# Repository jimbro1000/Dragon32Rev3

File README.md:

# DRAGON 32 RECREATION Rev 3 #

This project started as a recreation of the SA2120 CPU Mainboard
for the 1982 Dragon Data **Dragon 32**

Everything (excluding modifications) is taken from the SA2120
schematics. Where this version changes is that the options to
use banks of 16K DRAM is gone, you must use 64K DRAMs, with it
goes all the extra circuitry for configuring the memory for
different types of chip.

The ROM is now a single 27C256 eprom with an option to switch
between two images using JP6 or to allow the rom to be
automatically selected from the PIA.

A second ROM selection jumper is available at JP3 to be used
when a 27C512 is fitted. This swaps the value to A15 between
high and low. When a 27C256 is fitted this must be set low.

Hidden on the back of the board is a solder pad jumper (JP7) that
also needs setting to handle a 27C256 or 27C512. Bridging pad
1 sets pin 22 of the rom to ground, using pad 3 sets the
pin to use the ROM select signal shared with pin 20. When a
27C512 is fitted this must be set to pad 1.

The video circuits have been isolated from the rest of the
board to improve output quality.

A second (internal) cartridge port has been added, by way of
a 2x20 header, along with an additional +5V/Gnd pickup point
for further internal expansion.

An optional 256K banking solution is incorporated using the
design for Stewart Orchard's upgrade board and GAL design.
<https://gitlab.com/sorchard001/dragon-256k-banker-board>

## Progress ##

In the current state (3.3) most of the board is tested except
for the additional audio capabilities, SAMx8 compatibility and
the logic controlled switching of keyboard configuration.

## Modifications ##

### Joysticks ###

The two joystick ports provide a second fire button capability
wired to consecutive keyboard rows, as per the Tandy CoCo.
Unless a two button joystick is used this make no difference to
the operation of the computer. It also requires the use of 6-pin
DIN sockets, these are pin compatible with the 5-pin originals
so a regular single button joystick can still be used.

The two extra buttons can also be disabled by omitting L3 and L4.

### Parallel Port ###

A jumper (JP2) has been introduced to bypass the logic inverter
on the STROBE line. When bypassed the parallel port should
operate as a communication port for DRIVEWIRE.

### Memory Addressing ###

The board is configurable between 32k and 64k ram addressing
using jumper JP1. In most scenarios there is no reason to
disable the 64k option.

The upgrade to 256K needs the 4164s swapping for 41256s. The
pre-bridged jumper at JP5 needs cutting. The SAM also needs 
to be replaced with a 74LS785. The optional components can 
then be fitted and should work without further alteration.

The required JED file for the GAL22V10 that drives the memory
banking is in the CPLD folder of the project.

The 256K upgrade can be replaced with a SAMx8 upgrade board.
This replaces the SAM chip and the tristate buffer that sits
between the RAM and the CPU, and also allows connection to
the second data path that goes to the VDG. With this in place
the DRAM (either 4164 or 41256) is redundant, as is the GAL 
that provides the 256K banker capability.

### Video Port ###

The board includes a third connector for the video mezzanine
card. This exposes the video board to the CPU side of the
data bus along with control signals that would permit 
programming of the video for additional features. With a 
stock 6847 that might be to include a programmable character
"rom" but I'm also working on a synthetic FPGA based replacement
for the 6847 that will allow much bigger changes such as 
swappable/programmable colour palettes.

### Audio ###

The board provides a position to mount a custom implementation
of the AY sound generator. This provides three channels of 
synthesised sound without using the CPU intensive system that
the Dragon comes with by default. The capabilities are the same
as those of the Spectrum 128 models. You can even mix the old
and new methods of sound generation to create more noise!

Theoretically other sound generators could be used but the AY
option provides a cheap, capable mechanism that follows a 
standard familiar to users of other computers from the era.

### Keyboard ###

The board places a GAL chip between the input register of
PIA 1 and the keyboard connector. The GAL could be ommitted
and jumpers used to hardwire the connections to either
Dragon or CoCo compatibility.

With a GAL in place the wiring is controlled by a jumper.

## Substitutions ##

Many of the original components are simply unobtainable or
just very hard (and expensive) to locate. The transistors
will need modern substitutes as the BC141, BC212 and 2N2369
are all obsolete but thankfully these are fairly run-of-the-mill
transistors and shouldn't cause any particular issues.

The CPU and PIAs are all fairly easy to obtain online
and possibly even new (MC6821s are still made and there
are lots of compatible alternatives). A and B rated components
should all be usable but make sure the processor is an "09e".
The Hitachi HD6309 is usable but may cause crashes in some
software due to lazy coding.

Ciaran Anscomb's samX4 can be used to replace the SAM
chip and can be configured to operate as a 74LS783 or a
74LS785 to suit.

### The Future ###

As these parts become harder to find it is inevitable that
replacements and redesigns will be needed. After much hard
work by the Dragon and CoCo community the *only* IC on the
required, that is not still made or in plentiful supply is
the MC6847 VDG (the LM1889 on the PAL board is also in
limited supply but there are ways around the issue).

The Hitachi HD6309 has been in production until recently due
to military supply contracts making it easily accessible and
at reasonable cost. Ultimately this will diminish but with
supplies still high it seems likely to be available for a long
time yet.

The MC6821 is available new but at eye watering prices as
it is only made in small batches. The WD65C21 is a direct
swap and in much higher supply making it generally cheaper
than remaining original NOS parts.

The LS and CD discrete logic chips are all generally easy
to obtain and all have more modern equivalents that can be
swapped in.

Some searching may be needed for the cartridge port connector.
A direct replacement part is listed in the EDAC catalogue but
is only made to demand which requires an order of some 200
units. Lower quality but compatible parts can be found online.

Ultimately all of the parts will become hard to obtain but
for the foreseeable future the board should remain viable.

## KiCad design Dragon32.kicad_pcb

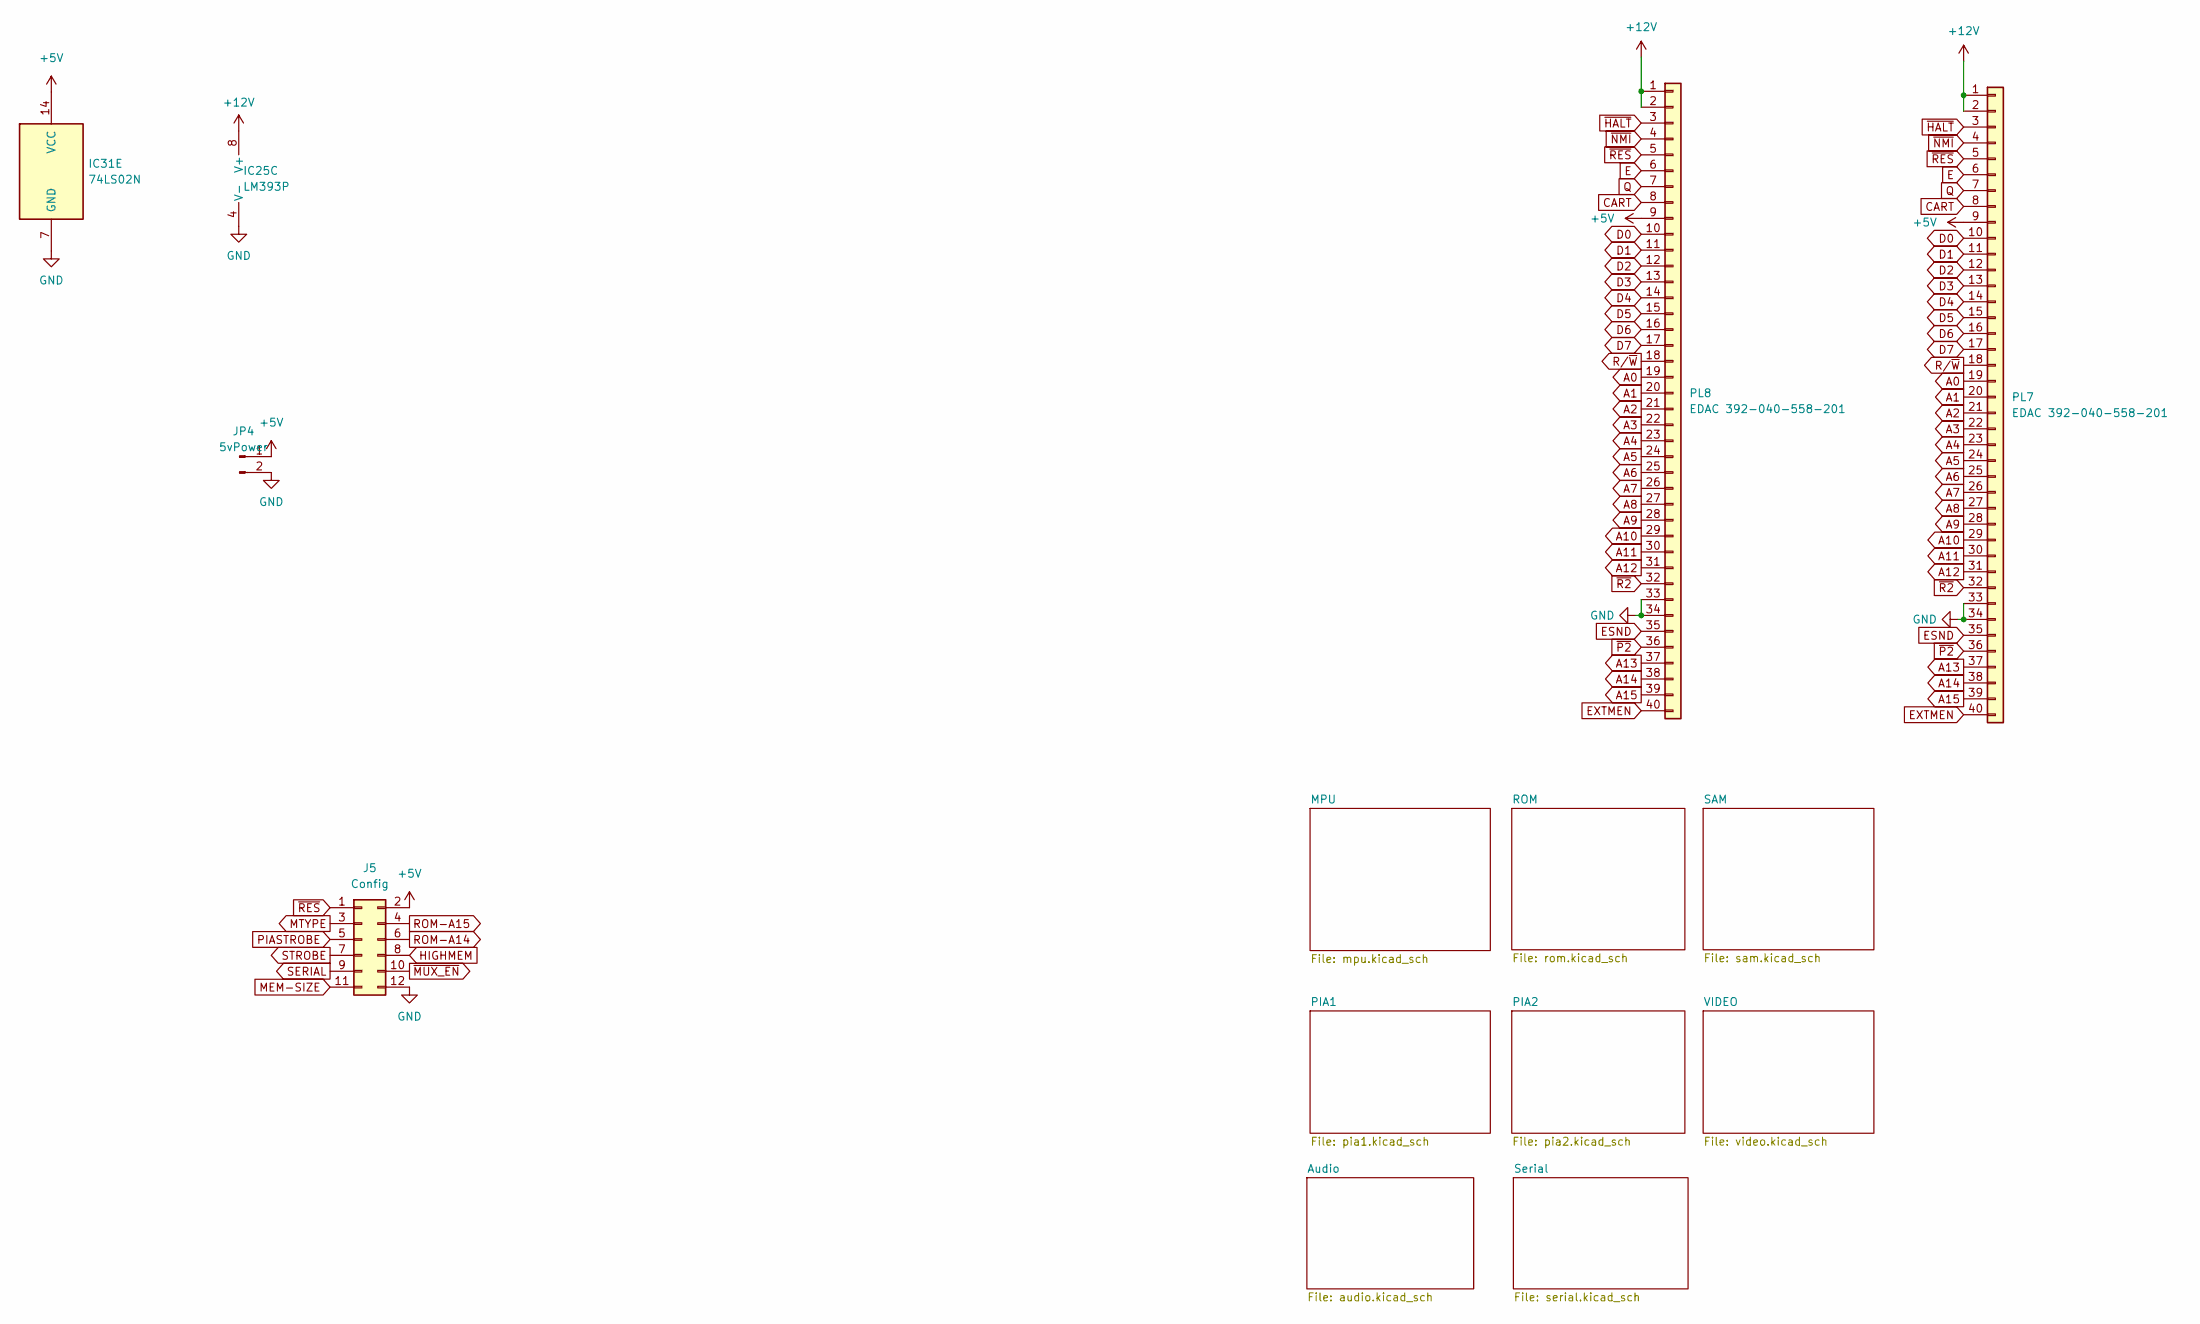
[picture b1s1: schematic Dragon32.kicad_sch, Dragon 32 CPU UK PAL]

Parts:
IC25: LM393P; DIP-8_W7.62mm; DigiKey 296-1398-5-ND
IC31: 74LS02N; DIP-14_W7.62mm; DigiKey 296-1627-5-ND
J5: Config; PinHeader_2x06_P2.54mm_Vertical
JP4: 5vPower; PinHeader_1x02_P2.54mm_Vertical
PL7: EDAC 392-040-558-201; Edge_2x20_P2.54mm_OvalMP; DigiKey 151-395-040-558-201-ND
PL8: EDAC 392-040-558-201; PinHeader_2x20_P2.54mm_Vertical; DigiKey 151-395-040-558-201-ND

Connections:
+5V: IC31.14 (VCC), J5.2, JP4.1, PL7.9, PL8.9; also elsewhere on the board
+12V: IC25.8 (V+), PL7.1, PL7.2, PL8.1, PL8.2; also elsewhere on the board
A0: PL7.19, PL8.19; also elsewhere on the board
A1: PL7.20, PL8.20; also elsewhere on the board
A2: PL7.21, PL8.21; also elsewhere on the board
A3: PL7.22, PL8.22; also elsewhere on the board
A4: PL7.23, PL8.23; also elsewhere on the board
A5: PL7.24, PL8.24; also elsewhere on the board
A6: PL7.25, PL8.25; also elsewhere on the board
A7: PL7.26, PL8.26; also elsewhere on the board
A8: PL7.27, PL8.27; also elsewhere on the board
A9: PL7.28, PL8.28; also elsewhere on the board
A10: PL7.29, PL8.29; also elsewhere on the board
A11: PL7.30, PL8.30; also elsewhere on the board
A12: PL7.31, PL8.31; also elsewhere on the board
A13: PL7.37, PL8.37; also elsewhere on the board
A14: PL7.38, PL8.38; also elsewhere on the board
A15: PL7.39, PL8.39; also elsewhere on the board
CART: PL7.8, PL8.8; also elsewhere on the board
D0: PL7.10, PL8.10; also elsewhere on the board
D1: PL7.11, PL8.11; also elsewhere on the board
D2: PL7.12, PL8.12; also elsewhere on the board
D3: PL7.13, PL8.13; also elsewhere on the board
D4: PL7.14, PL8.14; also elsewhere on the board
D5: PL7.15, PL8.15; also elsewhere on the board
D6: PL7.16, PL8.16; also elsewhere on the board
D7: PL7.17, PL8.17; also elsewhere on the board
E: PL7.6, PL8.6; also elsewhere on the board
ESND: PL7.35, PL8.35; also elsewhere on the board
EXTMEN: PL7.40, PL8.40; also elsewhere on the board
HIGHMEM: J5.8; also elsewhere on the board
MEM-SIZE: J5.11; also elsewhere on the board
MTYPE: J5.3; also elsewhere on the board
PIASTROBE: J5.5; also elsewhere on the board
Q: PL7.7, PL8.7; also elsewhere on the board
ROM-A14: J5.6; also elsewhere on the board
ROM-A15: J5.4; also elsewhere on the board
R/~W: PL7.18, PL8.18; also elsewhere on the board
SERIAL: J5.9; also elsewhere on the board
STROBE: J5.7; also elsewhere on the board
~HALT: PL7.3, PL8.3; also elsewhere on the board
~MUX_EN: J5.10; also elsewhere on the board
~NMI: PL7.4, PL8.4; also elsewhere on the board
~P2: PL7.36, PL8.36; also elsewhere on the board
~R2: PL7.32, PL8.32; also elsewhere on the board
~RES: J5.1, PL7.5, PL8.5; also elsewhere on the board

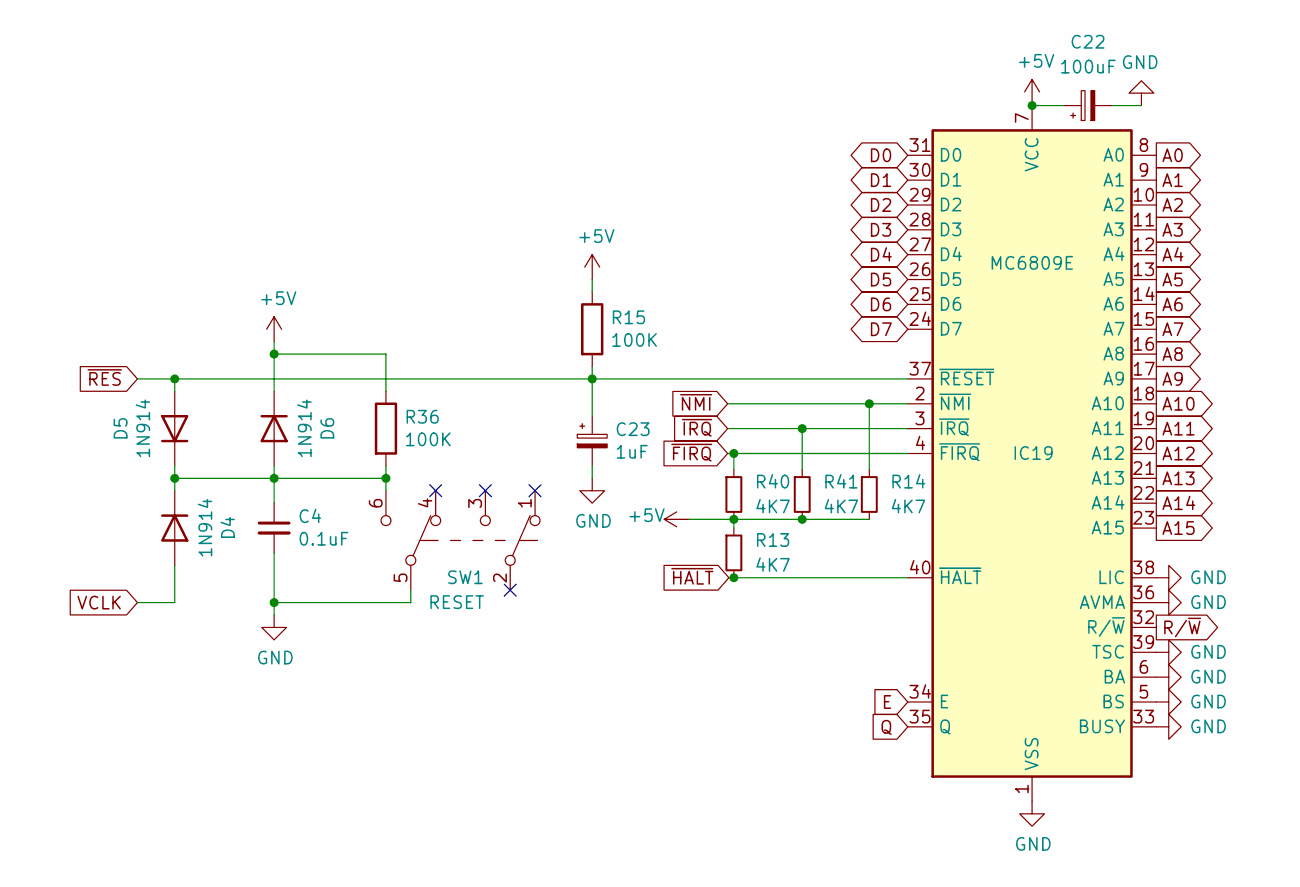
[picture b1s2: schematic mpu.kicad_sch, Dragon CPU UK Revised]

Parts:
C4: 0.1uF; C_Disc_D4.3mm_W1.9mm_P5.00mm; DigiKey BC1101CT-ND
C22: 100uF; CP_Radial_D6.3mm_P2.50mm; DigiKey 732-8598-1-ND
C23: 1uF; CP_Radial_D5.0mm_P2.50mm; DigiKey 732-8966-1-ND
D4, D5, D6: 1N914; D_DO-35_SOD27_P2.54mm_Vertical_KathodeUp; DigiKey 1N914FS-ND
IC19: MC6809E; DIP-40_W15.24mm
R13, R14, R40, R41: 4K7; R_Axial_DIN0207_L6.3mm_D2.5mm_P2.54mm_Vertical; DigiKey CF14JT4K70CT-ND
R15, R36: 100K; R_Axial_DIN0207_L6.3mm_D2.5mm_P2.54mm_Vertical; DigiKey CF14JT100KCT-ND
SW1: RESET; Button_AlpsAlpine_SPUN190900; DigiKey 401-1225-ND

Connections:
+5V: C22.1, D6.1 (K), IC19.7 (VCC), R13.1, R14.2, R15.1, R36.1, R40.2, R41.2; also elsewhere on the board
A0: IC19.8 (A0); also elsewhere on the board
A1: IC19.9 (A1); also elsewhere on the board
A2: IC19.10 (A2); also elsewhere on the board
A3: IC19.11 (A3); also elsewhere on the board
A4: IC19.12 (A4); also elsewhere on the board
A5: IC19.13 (A5); also elsewhere on the board
A6: IC19.14 (A6); also elsewhere on the board
A7: IC19.15 (A7); also elsewhere on the board
A8: IC19.16 (A8); also elsewhere on the board
A9: IC19.17 (A9); also elsewhere on the board
A10: IC19.18 (A10); also elsewhere on the board
A11: IC19.19 (A11); also elsewhere on the board
A12: IC19.20 (A12); also elsewhere on the board
A13: IC19.21 (A13); also elsewhere on the board
A14: IC19.22 (A14); also elsewhere on the board
A15: IC19.23 (A15); also elsewhere on the board
D0: IC19.31 (D0); also elsewhere on the board
D1: IC19.30 (D1); also elsewhere on the board
D2: IC19.29 (D2); also elsewhere on the board
D3: IC19.28 (D3); also elsewhere on the board
D4: IC19.27 (D4); also elsewhere on the board
D5: IC19.26 (D5); also elsewhere on the board
D6: IC19.25 (D6); also elsewhere on the board
D7: IC19.24 (D7); also elsewhere on the board
E: IC19.34 (E); also elsewhere on the board
unnamed: C4.1, D4.1 (K), D5.1 (K), D6.2 (A), R36.2, SW1.6 (C)
Q: IC19.35 (Q); also elsewhere on the board
R/~W: IC19.32 (R/~W); also elsewhere on the board
VCLK: D4.2 (A); also elsewhere on the board
~FIRQ: IC19.4 (~FIRQ), R40.1; also elsewhere on the board
~HALT: IC19.40 (~HALT), R13.2; also elsewhere on the board
~IRQ: IC19.3 (~IRQ), R41.1; also elsewhere on the board
~NMI: IC19.2 (~NMI), R14.1; also elsewhere on the board
~RES: C23.1, D5.2 (A), IC19.37 (~RESET), R15.2; also elsewhere on the board

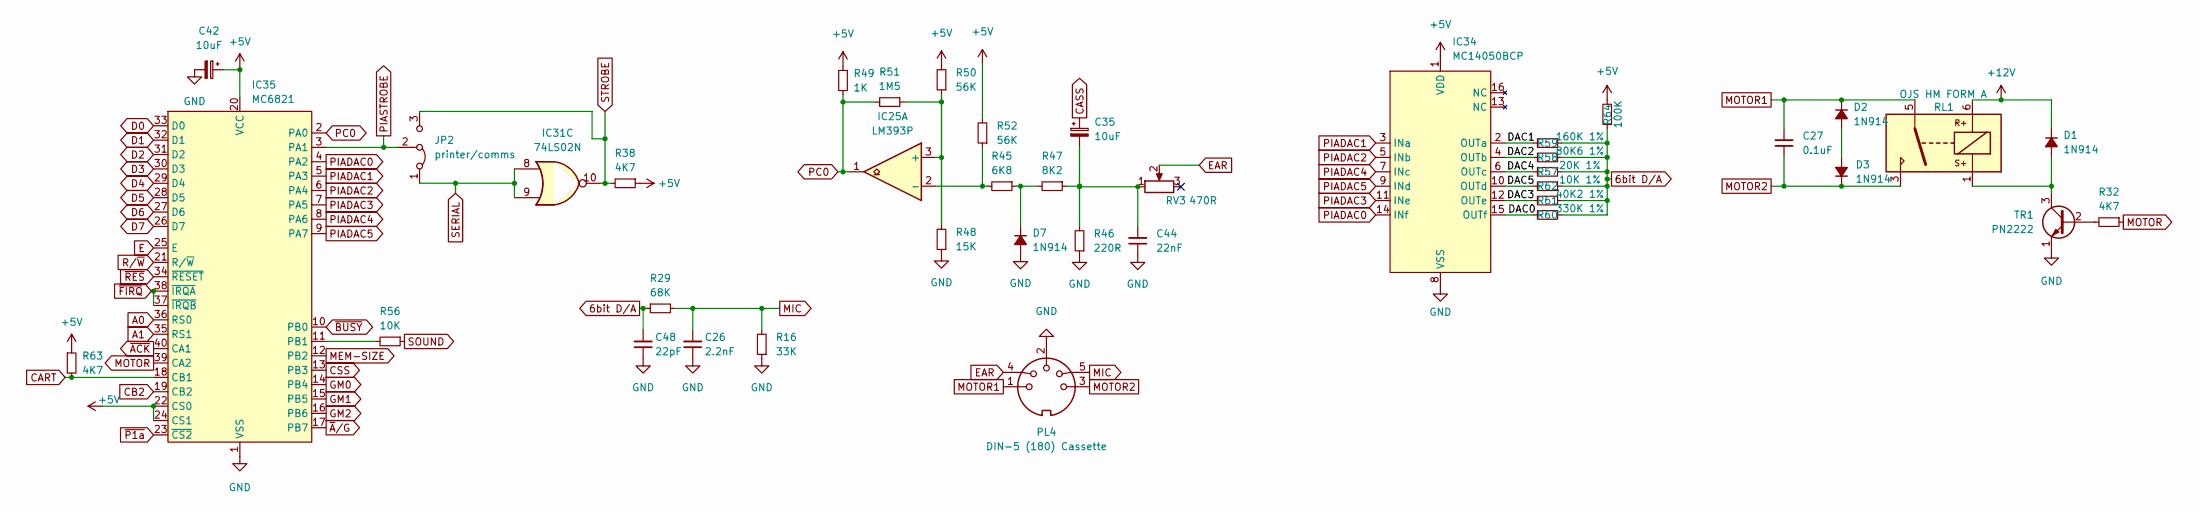
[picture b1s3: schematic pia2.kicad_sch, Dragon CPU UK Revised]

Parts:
C26: 2.2nF; C_Disc_D3.0mm_W2.0mm_P2.50mm; DigiKey BC1074CT-ND
C27: 0.1uF; C_Disc_D4.3mm_W1.9mm_P5.00mm; DigiKey BC1101CT-ND
C35, C42: 10uF; CP_Radial_D5.0mm_P2.50mm; DigiKey 732-8593-1-ND
C44: 22nF; C_Disc_D5.0mm_W2.5mm_P5.00mm; DigiKey BC2677CT-ND
C48: 22pF; C_Disc_D3.0mm_W2.0mm_P2.50mm; DigiKey 399-13930-1-ND
D1, D2, D3, D7: 1N914; D_DO-35_SOD27_P7.62mm_Horizontal; DigiKey 1N914FS-ND
IC25: LM393P; DIP-8_W7.62mm; DigiKey 296-1398-5-ND
IC31: 74LS02N; DIP-14_W7.62mm; DigiKey 296-1627-5-ND
IC34: MC14050BCP; DIP-16_W7.62mm; DigiKey 296-2056-ND
IC35: MC6821; DIP-40_W15.24mm; DigiKey 2156-MC6821CS-2156-ND
JP2: printer/comms; PinHeader_1x03_P2.54mm_Vertical
PL4: DIN-5 (180) Cassette; DIN-5_DELTRON_671-0501_45deg_Horizontal
R16: 33K; R_Axial_DIN0207_L6.3mm_D2.5mm_P2.54mm_Vertical; DigiKey CF14JT33K0CT-ND
R29: 68K; R_Axial_DIN0207_L6.3mm_D2.5mm_P10.16mm_Horizontal; DigiKey CF14JT68K0CT-ND
R32: 4K7; R_Axial_DIN0207_L6.3mm_D2.5mm_P2.54mm_Vertical; DigiKey CF14JT4K70CT-ND
R38, R63: 4K7; R_Axial_DIN0207_L6.3mm_D2.5mm_P10.16mm_Horizontal; DigiKey CF14JT4K70CT-ND
R45: 6K8; R_Axial_DIN0207_L6.3mm_D2.5mm_P10.16mm_Horizontal; DigiKey CF14JT6K80CT-ND
R46: 220R; R_Axial_DIN0207_L6.3mm_D2.5mm_P10.16mm_Horizontal; DigiKey CF14JT220RCT-ND
R47: 8K2; R_Axial_DIN0207_L6.3mm_D2.5mm_P10.16mm_Horizontal; DigiKey CF14JT8K20CT-ND
R48: 15K; R_Axial_DIN0207_L6.3mm_D2.5mm_P10.16mm_Horizontal; DigiKey CF14JT15K0CT-ND
R49: 1K; R_Axial_DIN0207_L6.3mm_D2.5mm_P10.16mm_Horizontal; DigiKey CF14JT1K00CT-ND
R50, R52: 56K; R_Axial_DIN0207_L6.3mm_D2.5mm_P10.16mm_Horizontal; DigiKey CF14JT56K0CT-ND
R51: 1M5; R_Axial_DIN0207_L6.3mm_D2.5mm_P10.16mm_Horizontal; DigiKey CF14JT1M50CT-ND
R56: 10K; R_Axial_DIN0207_L6.3mm_D2.5mm_P10.16mm_Horizontal; DigiKey CF14JT10K0CT-ND
R57: 20K 1%; R_Axial_DIN0207_L6.3mm_D2.5mm_P10.16mm_Horizontal; DigiKey RNF14FTD20K0CT-ND
R58: 80K6 1%; R_Axial_DIN0207_L6.3mm_D2.5mm_P10.16mm_Horizontal; DigiKey RNF14FTD80K6CT-ND
R59: 160K 1%; R_Axial_DIN0207_L6.3mm_D2.5mm_P10.16mm_Horizontal; DigiKey S160CACT-ND
R60: 330K 1%; R_Axial_DIN0207_L6.3mm_D2.5mm_P10.16mm_Horizontal; DigiKey S330KCACT-ND
R61: 40K2 1%; R_Axial_DIN0207_L6.3mm_D2.5mm_P10.16mm_Horizontal; DigiKey RNF14FTD41K2CT-ND
R62: 10K 1%; R_Axial_DIN0207_L6.3mm_D2.5mm_P10.16mm_Horizontal; DigiKey RNF14FTD10K0CT-ND
R64: 100K; R_Axial_DIN0207_L6.3mm_D2.5mm_P10.16mm_Horizontal; DigiKey CF14JT100KCT-ND
RL1: OJS HM FORM A; OJS HM 10A Relay; DigiKey 41-OJS-SH-105HMF,00000-ND
RV3: 470R; Potentiometer_Bourns_3386X_Horizontal; DigiKey 3386H-103LF-ND
TR1: PN2222; TO-92_Inline_Wide; DigiKey KSD1616AYTACT-ND

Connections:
6bit D/A: C48.2, R29.1, R57.1, R58.1, R59.1, R60.1, R61.1, R62.1, R64.1; also elsewhere on the board
+5V: C42.1, IC34.1 (VDD), IC35.20 (VCC), IC35.22 (CS0), IC35.24 (CS1), R38.1, R49.1, R50.2, R52.2, R63.1, R64.2; also elsewhere on the board
+12V: D1.1 (K), RL1.6; also elsewhere on the board
/PIA2/DAC0: IC34.15 (OUTf), R60.2
/PIA2/DAC1: IC34.2 (OUTa), R59.2
/PIA2/DAC2: IC34.4 (OUTb), R58.2
/PIA2/DAC3: IC34.12 (OUTe), R61.2
/PIA2/DAC4: IC34.6 (OUTc), R57.2
/PIA2/DAC5: IC34.10 (OUTd), R62.2
A0: IC35.36 (RS0); also elsewhere on the board
A1: IC35.35 (RS1); also elsewhere on the board
CART: IC35.18 (CB1), R63.2; also elsewhere on the board
CASS: C35.1; also elsewhere on the board
CB2: IC35.19 (CB2); also elsewhere on the board
CSS: IC35.13 (PB3); also elsewhere on the board
D0: IC35.33 (D0); also elsewhere on the board
D1: IC35.32 (D1); also elsewhere on the board
D2: IC35.31 (D2); also elsewhere on the board
D3: IC35.30 (D3); also elsewhere on the board
D4: IC35.29 (D4); also elsewhere on the board
D5: IC35.28 (D5); also elsewhere on the board
D6: IC35.27 (D6); also elsewhere on the board
D7: IC35.26 (D7); also elsewhere on the board
E: IC35.25 (E); also elsewhere on the board
EAR: PL4.4, RV3.2
GM0: IC35.14 (PB4); also elsewhere on the board
GM1: IC35.15 (PB5); also elsewhere on the board
GM2: IC35.16 (PB6); also elsewhere on the board
MEM-SIZE: IC35.12 (PB2); also elsewhere on the board
MIC: C26.2, PL4.5, R16.2, R29.2
MOTOR: IC35.39 (CA2), R32.1
MOTOR1: C27.2, D2.1 (K), PL4.1, RL1.5
MOTOR2: C27.1, D3.1 (K), PL4.3, RL1.3
unnamed: C35.2, C44.2, R46.2, R47.1, RV3.1
unnamed: D1.2 (A), RL1.1, TR1.3 (C)
unnamed: D2.2 (A), D3.2 (A)
unnamed: D7.1 (K), R45.1, R47.2
unnamed: IC25.3 (+), R48.2, R50.1, R51.1
unnamed: IC25.2 (-), R45.2, R52.1
unnamed: IC35.11 (PB1), R56.2
unnamed: R32.2, TR1.2 (B)
PC0: IC25.1, IC35.2 (PA0), R49.2, R51.2
PIADAC0: IC34.14 (INf), IC35.4 (PA2)
PIADAC1: IC34.3 (INa), IC35.5 (PA3)
PIADAC2: IC34.5 (INb), IC35.6 (PA4)
PIADAC3: IC34.11 (INe), IC35.7 (PA5)
PIADAC4: IC34.7 (INc), IC35.8 (PA6)
PIADAC5: IC34.9 (INd), IC35.9 (PA7)
PIASTROBE: IC35.3 (PA1), JP2.2 (C); also elsewhere on the board
R/~W: IC35.21 (R/~W); also elsewhere on the board
SERIAL: IC31.8, IC31.9, JP2.1 (A); also elsewhere on the board
SOUND: R56.1; also elsewhere on the board
STROBE: IC31.10, JP2.3 (B), R38.2; also elsewhere on the board
~ACK: IC35.40 (CA1); also elsewhere on the board
~A/G: IC35.17 (PB7); also elsewhere on the board
~BUSY: IC35.10 (PB0); also elsewhere on the board
~FIRQ: IC35.37 (~IRQB), IC35.38 (~IRQA); also elsewhere on the board
~P1a: IC35.23 (~CS2); also elsewhere on the board
~RES: IC35.34 (~RESET); also elsewhere on the board

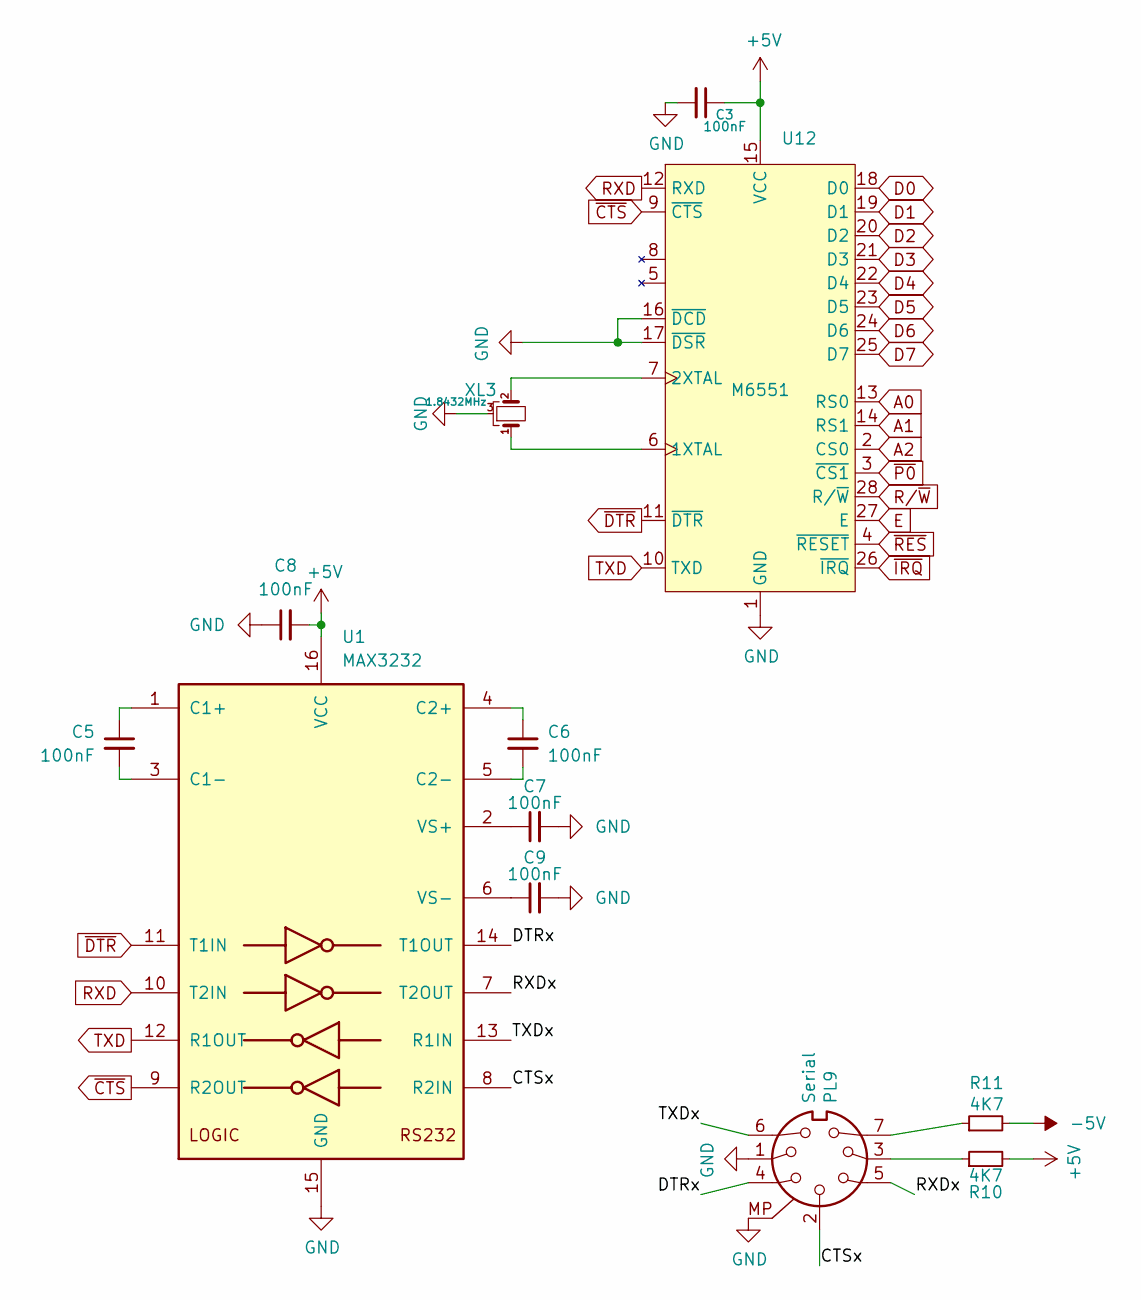
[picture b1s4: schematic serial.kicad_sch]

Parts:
C3, C5, C6, C7, C8, C9: 100nF; C_0805_2012Metric_Pad1.18x1.45mm_HandSolder; LCSC C1711
PL9: Serial; DIN-7_DELTRON_671-0701_Horizontal
R10, R11: 4K7; R_0805_2012Metric_Pad1.20x1.40mm_HandSolder; DigiKey CF14JT4K70CT-ND
U1: MAX3232; DIP-16_W7.62mm
U12: M6551; DIP-28_W15.24mm
XL3: 1.8432MHz; Crystal_HC18-U_Horizontal_1EP_style2

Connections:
+5V: C3.1, C8.2, R10.2, U1.16 (VCC), U12.15 (VCC); also elsewhere on the board
-5V: R11.2; also elsewhere on the board
/Serial/CTSx: PL9.2, U1.8 (R2IN)
/Serial/DTRx: PL9.4, U1.14 (T1OUT)
/Serial/RXDx: PL9.5, U1.7 (T2OUT)
/Serial/TXDx: PL9.6, U1.13 (R1IN)
A0: U12.13 (RS0); also elsewhere on the board
A1: U12.14 (RS1); also elsewhere on the board
A2: U12.2 (CS0); also elsewhere on the board
D0: U12.18 (D0); also elsewhere on the board
D1: U12.19 (D1); also elsewhere on the board
D2: U12.20 (D2); also elsewhere on the board
D3: U12.21 (D3); also elsewhere on the board
D4: U12.22 (D4); also elsewhere on the board
D5: U12.23 (D5); also elsewhere on the board
D6: U12.24 (D6); also elsewhere on the board
D7: U12.25 (D7); also elsewhere on the board
E: U12.27 (E); also elsewhere on the board
unnamed: PL9.3, R10.1
unnamed: PL9.7, R11.1
unnamed: C5.1, U1.1 (C1+)
unnamed: C5.2, U1.3 (C1-)
unnamed: C6.1, U1.4 (C2+)
unnamed: C6.2, U1.5 (C2-)
unnamed: C7.1, U1.2 (VS+)
unnamed: C9.1, U1.6 (VS-)
unnamed: U12.6 (1XTAL), XL3.1
unnamed: U12.7 (2XTAL), XL3.2
RXD: U1.10 (T2IN), U12.12 (RXD)
R/~W: U12.28 (R/~W); also elsewhere on the board
TXD: U1.12 (R1OUT), U12.10 (TXD)
~CTS: U1.9 (R2OUT), U12.9 (~CTS)
~DTR: U1.11 (T1IN), U12.11 (~DTR)
~IRQ: U12.26 (~IRQ); also elsewhere on the board
~P0: U12.3 (~CS1); also elsewhere on the board
~RES: U12.4 (~RESET); also elsewhere on the board

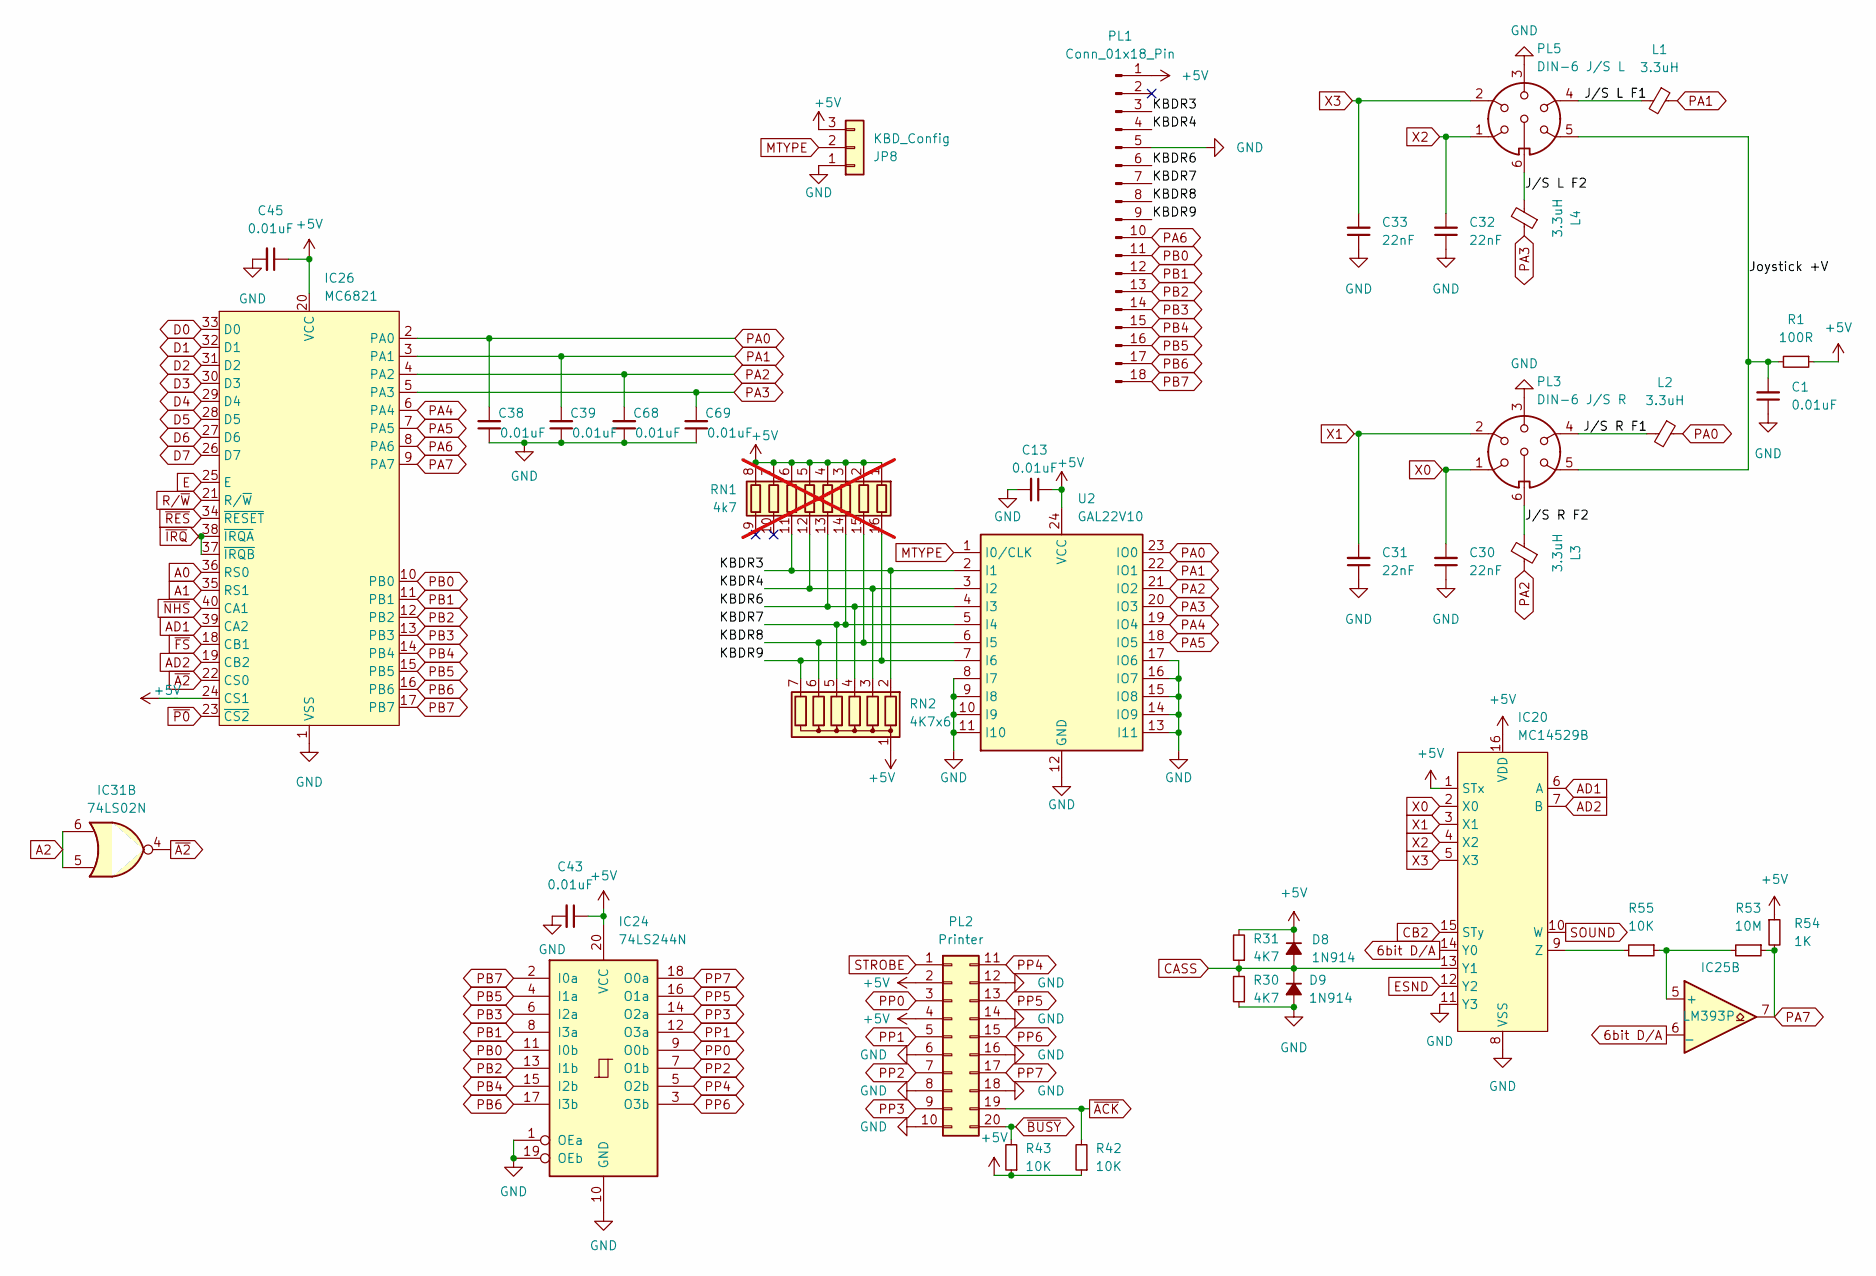
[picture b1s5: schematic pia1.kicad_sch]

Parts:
C1, C13, C43, C45: 0.01uF; C_Disc_D4.3mm_W1.9mm_P5.00mm; DigiKey BC2662CT-ND
C30, C31, C32, C33: 22nF; C_0805_2012Metric_Pad1.18x1.45mm_HandSolder; LCSC C1729
C38, C39, C68, C69: 0.01uF; C_Disc_D4.3mm_W1.9mm_P5.00mm; DigiKey BC1101CT-ND
D8, D9: 1N914; D_DO-35_SOD27_P7.62mm_Horizontal; DigiKey 1N914FS-ND
IC20: MC14529B; DIP-16_W7.62mm; DigiKey CD4529BCN-ND
IC24: 74LS244N; DIP-20_W7.62mm; DigiKey 296-1653-5-ND
IC25: LM393P; DIP-8_W7.62mm; DigiKey 296-1398-5-ND
IC26: MC6821; DIP-40_W15.24mm; DigiKey 2156-MC6821CS-2156-ND
IC31: 74LS02N; DIP-14_W7.62mm; DigiKey 296-1627-5-ND
JP8: KBD_Config; PinHeader_1x03_P2.54mm_Vertical
L1, L2, L3, L4: 3.3uH; L_Axial_L7.0mm_D3.3mm_P5.08mm_Vertical_Fastron_MICC; DigiKey 495-5561-1-ND
PL1: Conn_01x18_Pin; PinHeader_1x18_P2.54mm_Vertical
PL2: Printer; IDC-Header_2x10-1MP_P2.54mm_Latch_Horizontal; DigiKey CHR20G-ND
PL3: DIN-6 J/S R; DIN-6_DELTRON_671-0601_Horizontal
PL5: DIN-6 J/S L; DIN-6_DELTRON_671-0601_Horizontal
R1: 100R; R_Axial_DIN0207_L6.3mm_D2.5mm_P10.16mm_Horizontal; DigiKey CF14JT100RCT-ND
R30, R31: 4K7; R_Axial_DIN0207_L6.3mm_D2.5mm_P2.54mm_Vertical; DigiKey CF14JT4K70CT-ND
R42, R43, R55: 10K; R_Axial_DIN0207_L6.3mm_D2.5mm_P10.16mm_Horizontal; DigiKey CF14JT10K0CT-ND
R53: 10M; R_Axial_DIN0207_L6.3mm_D2.5mm_P10.16mm_Horizontal; DigiKey CF14JT10M0CT-ND
R54: 1K; R_Axial_DIN0207_L6.3mm_D2.5mm_P10.16mm_Horizontal; DigiKey CF14JT1K00CT-ND
RN1: 4k7; R_Array_Convex_8x0602; DigiKey Y1472CT-ND; not fitted
RN2: 4K7x6; R_Array_SIP7; LCSC C39096
U2: GAL22V10; DIP-24_W7.62mm

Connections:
6bit D/A: IC20.14 (Y0), IC25.6 (_); also elsewhere on the board
+5V: C13.1, C43.1, C45.1, D8.1 (K), IC20.1 (STx), IC20.16 (VDD), IC24.20 (VCC), IC26.20 (VCC), IC26.24 (CS1), JP8.3, PL1.1, PL2.2, PL2.4, R1.1, R31.2, R42.1, R43.1, R54.1, RN1.1 (R1.1), RN1.2 (R2.1), RN1.3 (R3.1), RN1.4 (R4.1), RN1.5 (R5.1), RN1.6 (R6.1), RN1.7 (R7.1), RN1.8 (R8.1), RN2.1 (common), U2.24 (VCC); also elsewhere on the board
/PIA1/Joystick +V: C1.2, PL3.5, PL5.5, R1.2
/PIA1/J/S L F1: L1.2, PL5.4
/PIA1/J/S L F2: L4.2, PL5.6
/PIA1/J/S R F1: L2.2, PL3.4
/PIA1/J/S R F2: L3.2, PL3.6
/PIA1/KBDR3: PL1.3, RN1.11 (R6.2), RN2.2 (R1), U2.2 (I1)
/PIA1/KBDR4: PL1.4, RN1.12 (R5.2), RN2.3 (R2), U2.3 (I2)
/PIA1/KBDR6: PL1.6, RN1.13 (R4.2), RN2.4 (R3), U2.4 (I3)
/PIA1/KBDR7: PL1.7, RN1.14 (R3.2), RN2.5 (R4), U2.5 (I4)
/PIA1/KBDR8: PL1.8, RN1.15 (R2.2), RN2.6 (R5), U2.6 (I5)
/PIA1/KBDR9: PL1.9, RN1.16 (R1.2), RN2.7 (R6), U2.7 (I6)
A0: IC26.36 (RS0); also elsewhere on the board
A1: IC26.35 (RS1); also elsewhere on the board
A2: IC31.5, IC31.6; also elsewhere on the board
AD1: IC20.6 (A), IC26.39 (CA2)
AD2: IC20.7 (B), IC26.19 (CB2)
CASS: D8.2 (A), D9.1 (K), IC20.13 (Y1), R30.2, R31.1; also elsewhere on the board
CB2: IC20.15 (STy); also elsewhere on the board
D0: IC26.33 (D0); also elsewhere on the board
D1: IC26.32 (D1); also elsewhere on the board
D2: IC26.31 (D2); also elsewhere on the board
D3: IC26.30 (D3); also elsewhere on the board
D4: IC26.29 (D4); also elsewhere on the board
D5: IC26.28 (D5); also elsewhere on the board
D6: IC26.27 (D6); also elsewhere on the board
D7: IC26.26 (D7); also elsewhere on the board
E: IC26.25 (E); also elsewhere on the board
ESND: IC20.12 (Y2); also elsewhere on the board
MTYPE: JP8.2, U2.1 (I0/CLK); also elsewhere on the board
unnamed: IC20.9 (Z), R55.2
unnamed: IC25.5 (+), R53.2, R55.1
PA0: C38.2, IC26.2 (PA0), L2.1, U2.23 (IO0)
PA1: C39.2, IC26.3 (PA1), L1.1, U2.22 (IO1)
PA2: C68.2, IC26.4 (PA2), L3.1, U2.21 (IO2)
PA3: C69.2, IC26.5 (PA3), L4.1, U2.20 (IO3)
PA4: IC26.6 (PA4), U2.19 (IO4)
PA5: IC26.7 (PA5), U2.18 (IO5)
PA6: IC26.8 (PA6), PL1.10
PA7: IC25.7, IC26.9 (PA7), R53.1, R54.2
PB0: IC24.11 (I0b), IC26.10 (PB0), PL1.11
PB1: IC24.8 (I3a), IC26.11 (PB1), PL1.12
PB2: IC24.13 (I1b), IC26.12 (PB2), PL1.13
PB3: IC24.6 (I2a), IC26.13 (PB3), PL1.14
PB4: IC24.15 (I2b), IC26.14 (PB4), PL1.15
PB5: IC24.4 (I1a), IC26.15 (PB5), PL1.16
PB6: IC24.17 (I3b), IC26.16 (PB6), PL1.17
PB7: IC24.2 (I0a), IC26.17 (PB7), PL1.18
PP0: IC24.9 (O0b), PL2.3
PP1: IC24.12 (O3a), PL2.5
PP2: IC24.7 (O1b), PL2.7
PP3: IC24.14 (O2a), PL2.9
PP4: IC24.5 (O2b), PL2.11
PP5: IC24.16 (O1a), PL2.13
PP6: IC24.3 (O3b), PL2.15
PP7: IC24.18 (O0a), PL2.17
R/~W: IC26.21 (R/~W); also elsewhere on the board
SOUND: IC20.10 (W); also elsewhere on the board
STROBE: PL2.1; also elsewhere on the board
X0: C30.2, IC20.2 (X0), PL3.1
X1: C31.2, IC20.3 (X1), PL3.2
X2: C32.2, IC20.4 (X2), PL5.1
X3: C33.2, IC20.5 (X3), PL5.2
~A2: IC26.22 (CS0), IC31.4
~ACK: PL2.19, R42.2; also elsewhere on the board
~BUSY: PL2.20, R43.2; also elsewhere on the board
~FS: IC26.18 (CB1); also elsewhere on the board
~IRQ: IC26.37 (~IRQB), IC26.38 (~IRQA); also elsewhere on the board
~NHS: IC26.40 (CA1); also elsewhere on the board
~P0: IC26.23 (~CS2); also elsewhere on the board
~RES: IC26.34 (~RESET); also elsewhere on the board
